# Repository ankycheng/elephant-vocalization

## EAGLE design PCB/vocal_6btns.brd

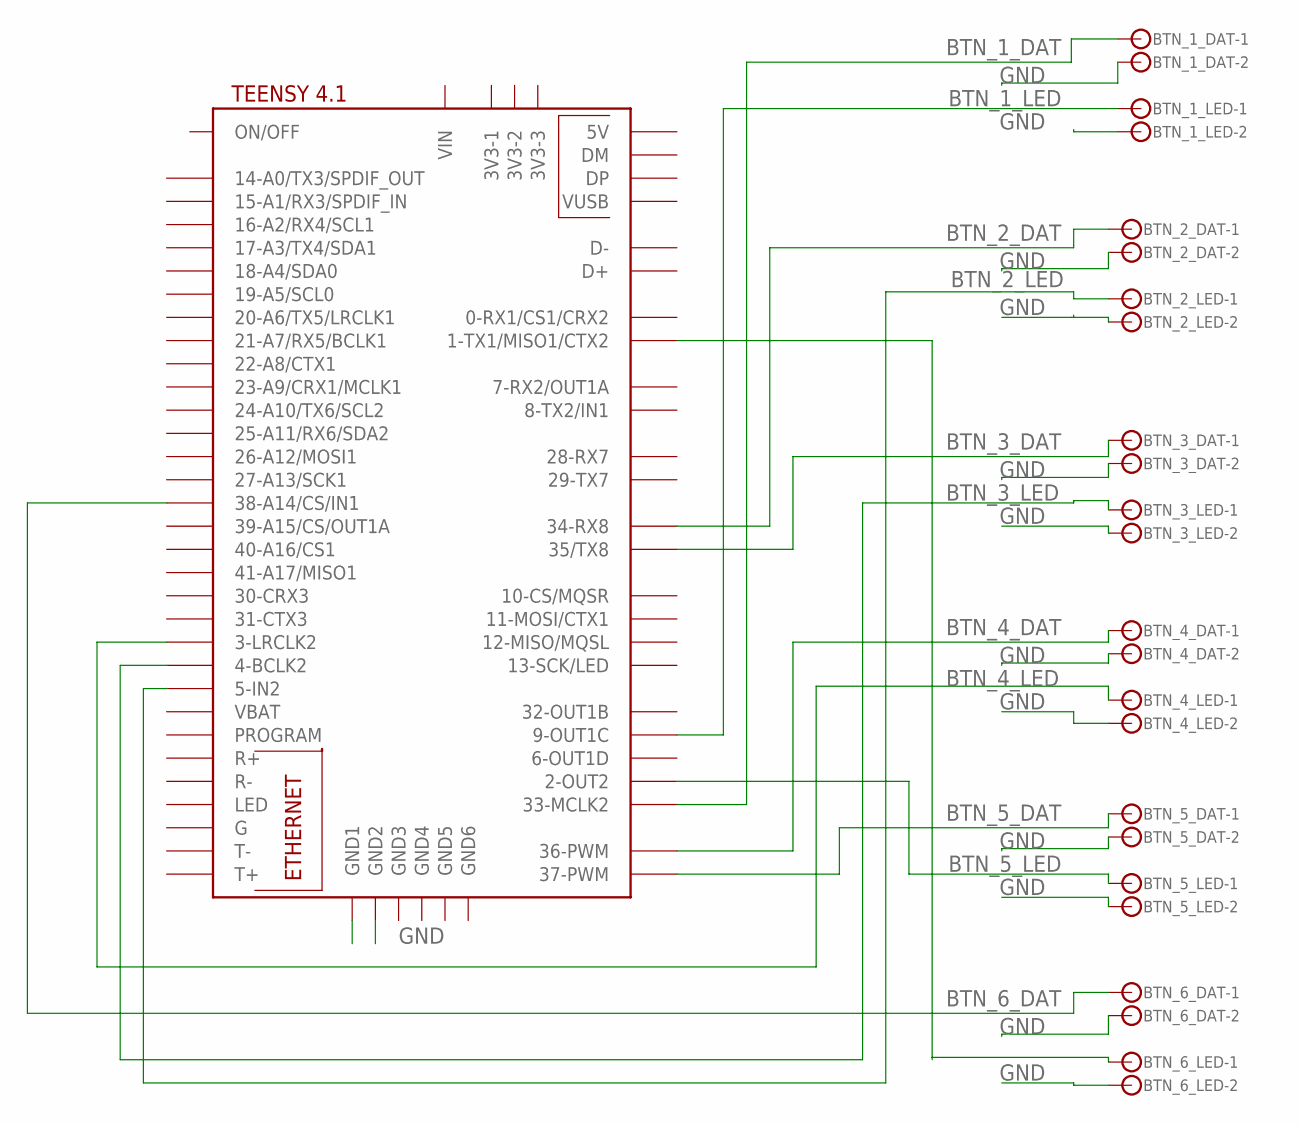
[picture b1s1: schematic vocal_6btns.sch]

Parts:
BTN_1_DAT, BTN_1_LED, BTN_2_DAT, BTN_2_LED, BTN_3_DAT, BTN_3_LED, BTN_4_DAT, BTN_4_LED, BTN_5_DAT, BTN_5_LED, BTN_6_DAT, BTN_6_LED: JST-XH-2B; B2B-XH-A
U$1: TEENSY41

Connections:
BTN_1_DAT: BTN_1_DAT.1, U$1.33-MCLK2
BTN_1_LED: BTN_1_LED.1, U$1.9-OUT1C
BTN_2_DAT: BTN_2_DAT.1, U$1.34-RX8
BTN_2_LED: BTN_2_LED.1, U$1.5-IN2
BTN_3_DAT: BTN_3_DAT.1, U$1.35-TX8 (35/TX8)
BTN_3_LED: BTN_3_LED.1, U$1.4-BCLK2
BTN_4_DAT: BTN_4_DAT.1, U$1.36-PWM
BTN_4_LED: BTN_4_LED.1, U$1.3-LRCLK2
BTN_5_DAT: BTN_5_DAT.1, U$1.37-PWM
BTN_5_LED: BTN_5_LED.1, U$1.2-OUT2
BTN_6_DAT: BTN_6_DAT.1, U$1.38-A14/CS/IN1
GND: BTN_1_DAT.2, BTN_1_LED.2, BTN_2_DAT.2, BTN_2_LED.2, BTN_3_DAT.2, BTN_3_LED.2, BTN_4_DAT.2, BTN_4_LED.2, BTN_5_DAT.2, BTN_5_LED.2, BTN_6_DAT.2, BTN_6_LED.2, U$1.GND1, U$1.GND2
unnamed: BTN_6_LED.1, U$1.1-TX1/MISO1/CTX2

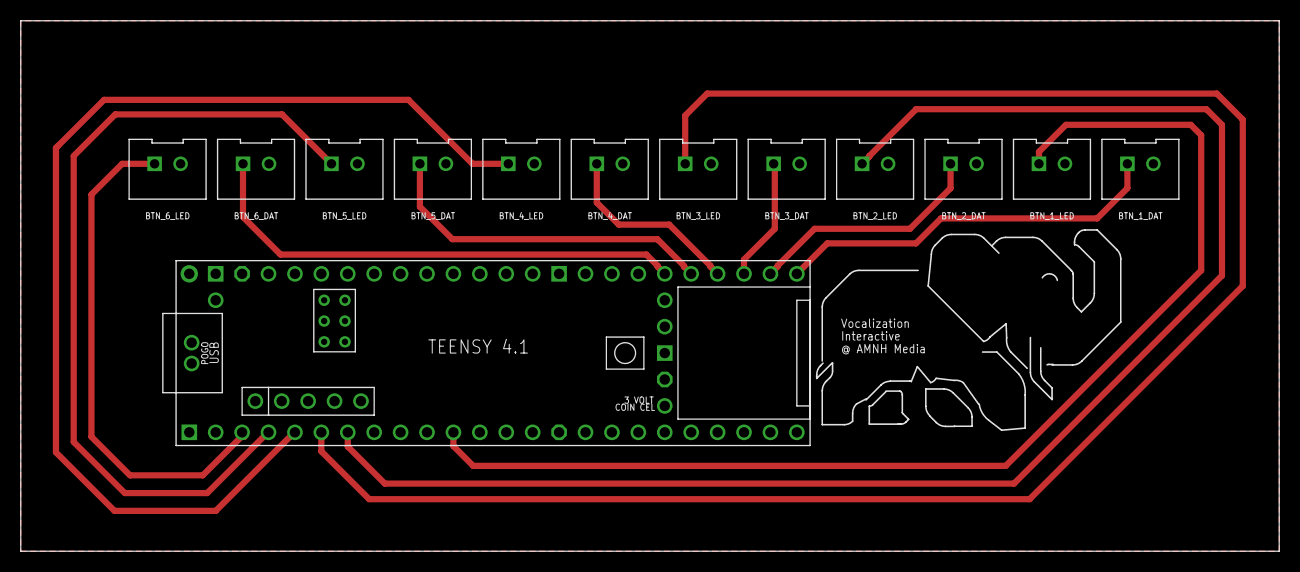
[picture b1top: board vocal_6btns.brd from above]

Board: 2 copper layers, 121.0 x 51.0 mm, 13 parts (0 on the bottom side), 13 nets.

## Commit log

2023-11-15 Chore: clean up code
2023-11-29 Update PCB files
2023-11-29 Update gerber files
